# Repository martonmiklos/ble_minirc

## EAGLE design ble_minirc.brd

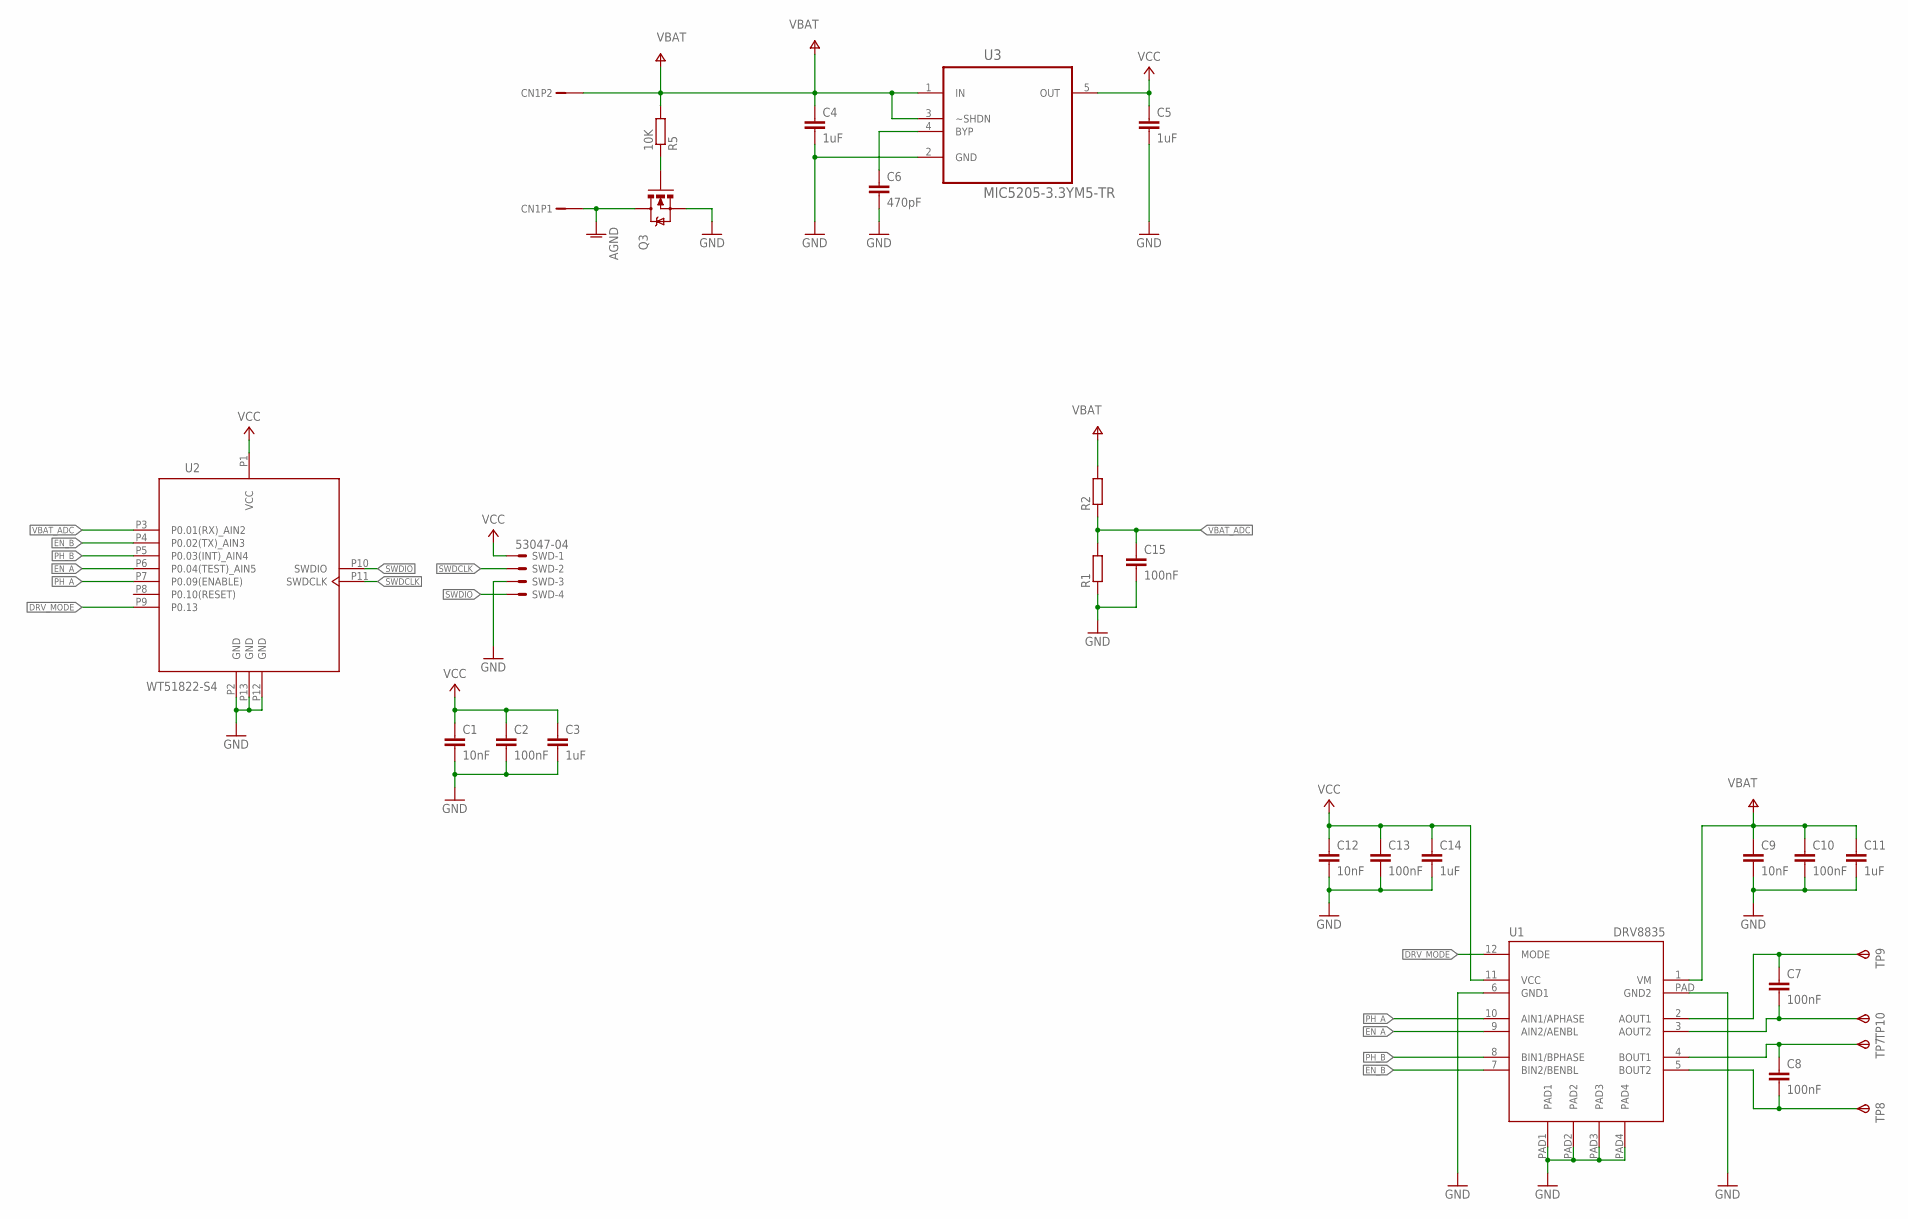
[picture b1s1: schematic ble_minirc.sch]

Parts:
C1, C9, C12: 10nF; C0603
C2, C7, C8, C10, C13, C15: 100nF; C0603
C3, C4, C5, C11, C14: 1uF; C0603
C6: 470pF; C0603
CN1: B2B-PH-K-S
Q3: MOSFET-NCHANNELSMD; SOT23-3
R1, R2: R-EU_R0603; R0603
R5: 10K; R0603
SWD: 53047-04
TP7, TP8, TP9, TP10: TPSB1,27; B1,27
U1: DRV8835; WSON_2X3
U2: WT51822-S4; WT51822-S4AT
U3: MIC5205-3.3YM5-TR; SOT95P280X145-5N

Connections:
A1: C7.1, TP9.TP, U1.2 (AOUT1)
A2: C7.2, TP10.TP, U1.3 (AOUT2)
AGND: CN1.1, Q3.3 (D)
ANTISTUPID_GATE: Q3.1 (G), R5.1
B1: C8.1, TP7.TP, U1.4 (BOUT1)
B2: C8.2, TP8.TP, U1.5 (BOUT2)
DRV_MODE: U1.12 (MODE), U2.P9 (P0.13)
EN_A: U1.9 (AIN2/AENBL), U2.P6 (P0.04(TEST)_AIN5)
EN_B: U1.7 (BIN2/BENBL), U2.P4 (P0.02(TX)_AIN3)
GND: C1.2, C2.2, C3.2, C4.2, C5.2, C6.2, C9.2, C10.2, C11.2, C12.2, C13.2, C14.2, C15.2, Q3.2 (S), R1.1, SWD.3, U1.6 (GND1), U1.PAD (GND2), U1.PAD1, U1.PAD2, U1.PAD3, U1.PAD4, U2.P2 (GND), U2.P12 (GND), U2.P13 (GND), U3.2 (GND)
MIC_BYPASS: C6.1, U3.4 (BYP)
PH_A: U1.10 (AIN1/APHASE), U2.P7 (P0.09(ENABLE))
PH_B: U1.8 (BIN1/BPHASE), U2.P5 (P0.03(INT)_AIN4)
SWDCLK: SWD.2, U2.P11 (SWDCLK)
SWDIO: SWD.4, U2.P10 (SWDIO)
VBAT: C4.1, C9.1, C10.1, C11.1, CN1.2, R2.2, R5.2, U1.1 (VM), U3.1 (IN), U3.3 (~SHDN)
VBAT_ADC: C15.1, R1.2, R2.1, U2.P3 (P0.01(RX)_AIN2)
VCC: C1.1, C2.1, C3.1, C5.1, C12.1, C13.1, C14.1, SWD.1, U1.11 (VCC), U2.P1 (VCC), U3.5 (OUT)

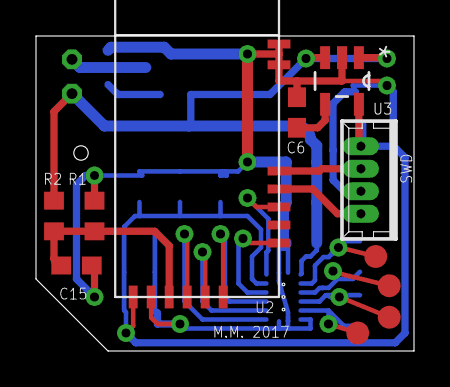
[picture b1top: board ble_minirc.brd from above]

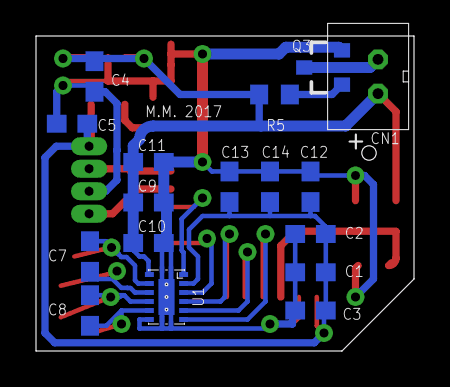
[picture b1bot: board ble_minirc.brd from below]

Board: 2 copper layers, 21.0 x 17.5 mm, 28 parts (17 on the bottom side), 18 nets.

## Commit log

2017-12-27 Added EAGLE files
2017-12-27 Silkscreen cleanup
2018-04-25 Fixed FET direction

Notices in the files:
parts and their libraries:
SparkFun: Licensing: CC v3.0 Share-Alike You are welcome to use this library for commercial purposes.
